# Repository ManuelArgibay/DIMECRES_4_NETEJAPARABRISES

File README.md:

# LIMPIA PARABRISAS

## Autores
- ManuelArgibay
- AlexY0916

## Versión - v1.01 Curso - Asignatura de Diseño de PCBs con KiCad - Curso 2024 - 2025

## Objectivo, Descripción breve del objectivo del proyecto.
Diseñar una placa PCB que desarrolle la función de limpiaparabrisas de un automóvil, mediante la detección de lluvia y accionamiento de motores, bombas de agua y un calefactor. Con el objetivo de mantener el parabrisas limpio y libre de objetos que puedan dificultar la visibilidad y evitar accidentes 

## Requisitos y especificaciones
- 2 motores con finales de carrera
- 2 bombas de líquido limpia parabrisas
- Sensor digital de lluvia
- Calefactor del vidrio

## Diagrama de bloques

## Tabla de componentes
| Descripción | Manufacturer Number | Package | Datasheet | Proveedor | Unidades |
| Microcontrolador | PIC18F258 | SOIC-28 | https://www.mouser.es/ProductDetail/Microchip-Technology/PIC18F258-I-SP?qs=uMUszenkLLIixFKqjRA69Q%3D%3D&srsltid=AfmBOopKXQlyaGkKwKApGVeNytftWyBSKV1Xqn-g4o59TgY9E8kJ9XiY | Mouser | 1 |
|Transceptor|MCP2551|SOIC-8|https://ww1.microchip.com/downloads/en/devicedoc/20001667g.pdf|Microchip|1|
|Amplificador operacional|LT1716|SOIC-5|https://www.mouser.es/datasheet/2/609/LT1716-1716222.pdf|Mouser|2|
|Regulador de tensión|LM117|TO-220|https://www.ti.com/lit/ds/symlink/lm1117.pdf?ts=1742942595976&ref_url=https%253A%252F%252Fbr.mouser.com%252F|Mouser|1|
|Puente H|DRV8871DDA|DDA|https://www.ti.com/lit/ds/symlink/drv8871-q1.pdf?ts=1742988697362&ref_url=https%253A%252F%252Fwww.ti.com%252Fproduct%252FDRV8871-Q1||2|

## Funcionalidades
- Control de motores de limpiaparabrisas, bomba de agua y calefactor
- Detección de lluvia mediante sensor
- Botonera de acción manual

## Historial de cambios | Fecha | Autor | Branch | Descripción |
|1|25/03/2025|ManuelArgibay|main|Creación del proyecto|
|2|25/03/2025|ManuelArgibay|main|Cambio titulo del proyecto|
|3|25/03/2025|ManuelArgibay|main|Modificación del esquemático y pptx|
|4|25/03/2025|ManuelArgibay|main|Agrego net classes, proyecto y presentación |
|5|25/03/2025|AlexY0916|main|Modifico net classes, fc, GNDPWR, separación botonera|
|6|26/03/2025|AlexY0916|main|Separacion del circuito|
|7|29/03/2025|ManuelArgibay|main|Agrego presentaciones y archivos|
|8|29/03/2025|ManuelArgibay|main|Modifico simulaciones del comparador y arreglo esquematico|
|9|30/03/2025|AlexY0916|main|Ordenar esquematico|
|10|30/03/2025|AlexY0916|main|Footprint|
|11|30/03/2025|AlexY0916|main|Arreglar errores con los esquematicos|
|12|30/03/2025|AlexY0916|main|Empezando a añadir el sensor|
|13|31/03/2025|AlexY0916|main|Sensor|
|14|31/03/2025|AlexY0916|main|ICSP|
|15|31/03/2025|ManuelArgibay|main|Arreglo net classes y agrego DB-9|
|16|31/03/2025|ManuelArgibay|main|Empiezo layout, cambio footprints y arreglo esquematico|
|17|01/04/2025|ManuelArgibay|main|Termino layout|
|18|01/04/2025|ManuelArgibay|main|Arreglo nodos no conectados|
|19|01/04/2025|AlexY0916|main|Cambio el cristal|
|20|01/04/2025|AlexY0916|main|Cambio de presentacion, minimas correcciones en el esquematico|
|21|01/04/2025|AlexY0916|main|Nombrar etiqueta PCB|
|22|01/04/2025|AlexY0916|main|Cambio en la presentacion|
|23|02/04/2025|ManuelArgibay|main|Arreglo errores y cambio conector|
|24|02/04/2025|ManuelArgibay|main|Arreglo errores del DRC. Falta arreglar errores del GNDPWR|
|25|02/04/2025|ManuelArgibay|main|Preentrega final|
|26|02/04/2025|ManuelArgibay|main|Agrego cambios|
|27|07/04/2025|ManuelArgibay|main|Arreglo layout y esquematico con las correcciones pasadas|
|28|07/04/2025|AlexY0916|main|Separacion de la botonera|
|29|07/04/2025|AlexY0916|main|Cambio de valor los condensadores del oscilador|
|30|07/04/2025|AlexY0916|main|Cambio diagrama de bloques|
|31|08/04/2025|AlexY0916|main|Reglas de diseño|
|32|08/04/2025|AlexY0916|main|Cambiar esquematico|
|33|08/04/2025|AlexY0916|main|Cambio de la PCB (cambio de conectores)|
|34|09/04/2025|AlexY0916|main|Layout|
|35|09/04/2025|AlexY0916|main|Cambio del sensor|
|36|23/04/2025|ManuelArgibay|main|Arreglo layout y esquematico (DRC correcto)|

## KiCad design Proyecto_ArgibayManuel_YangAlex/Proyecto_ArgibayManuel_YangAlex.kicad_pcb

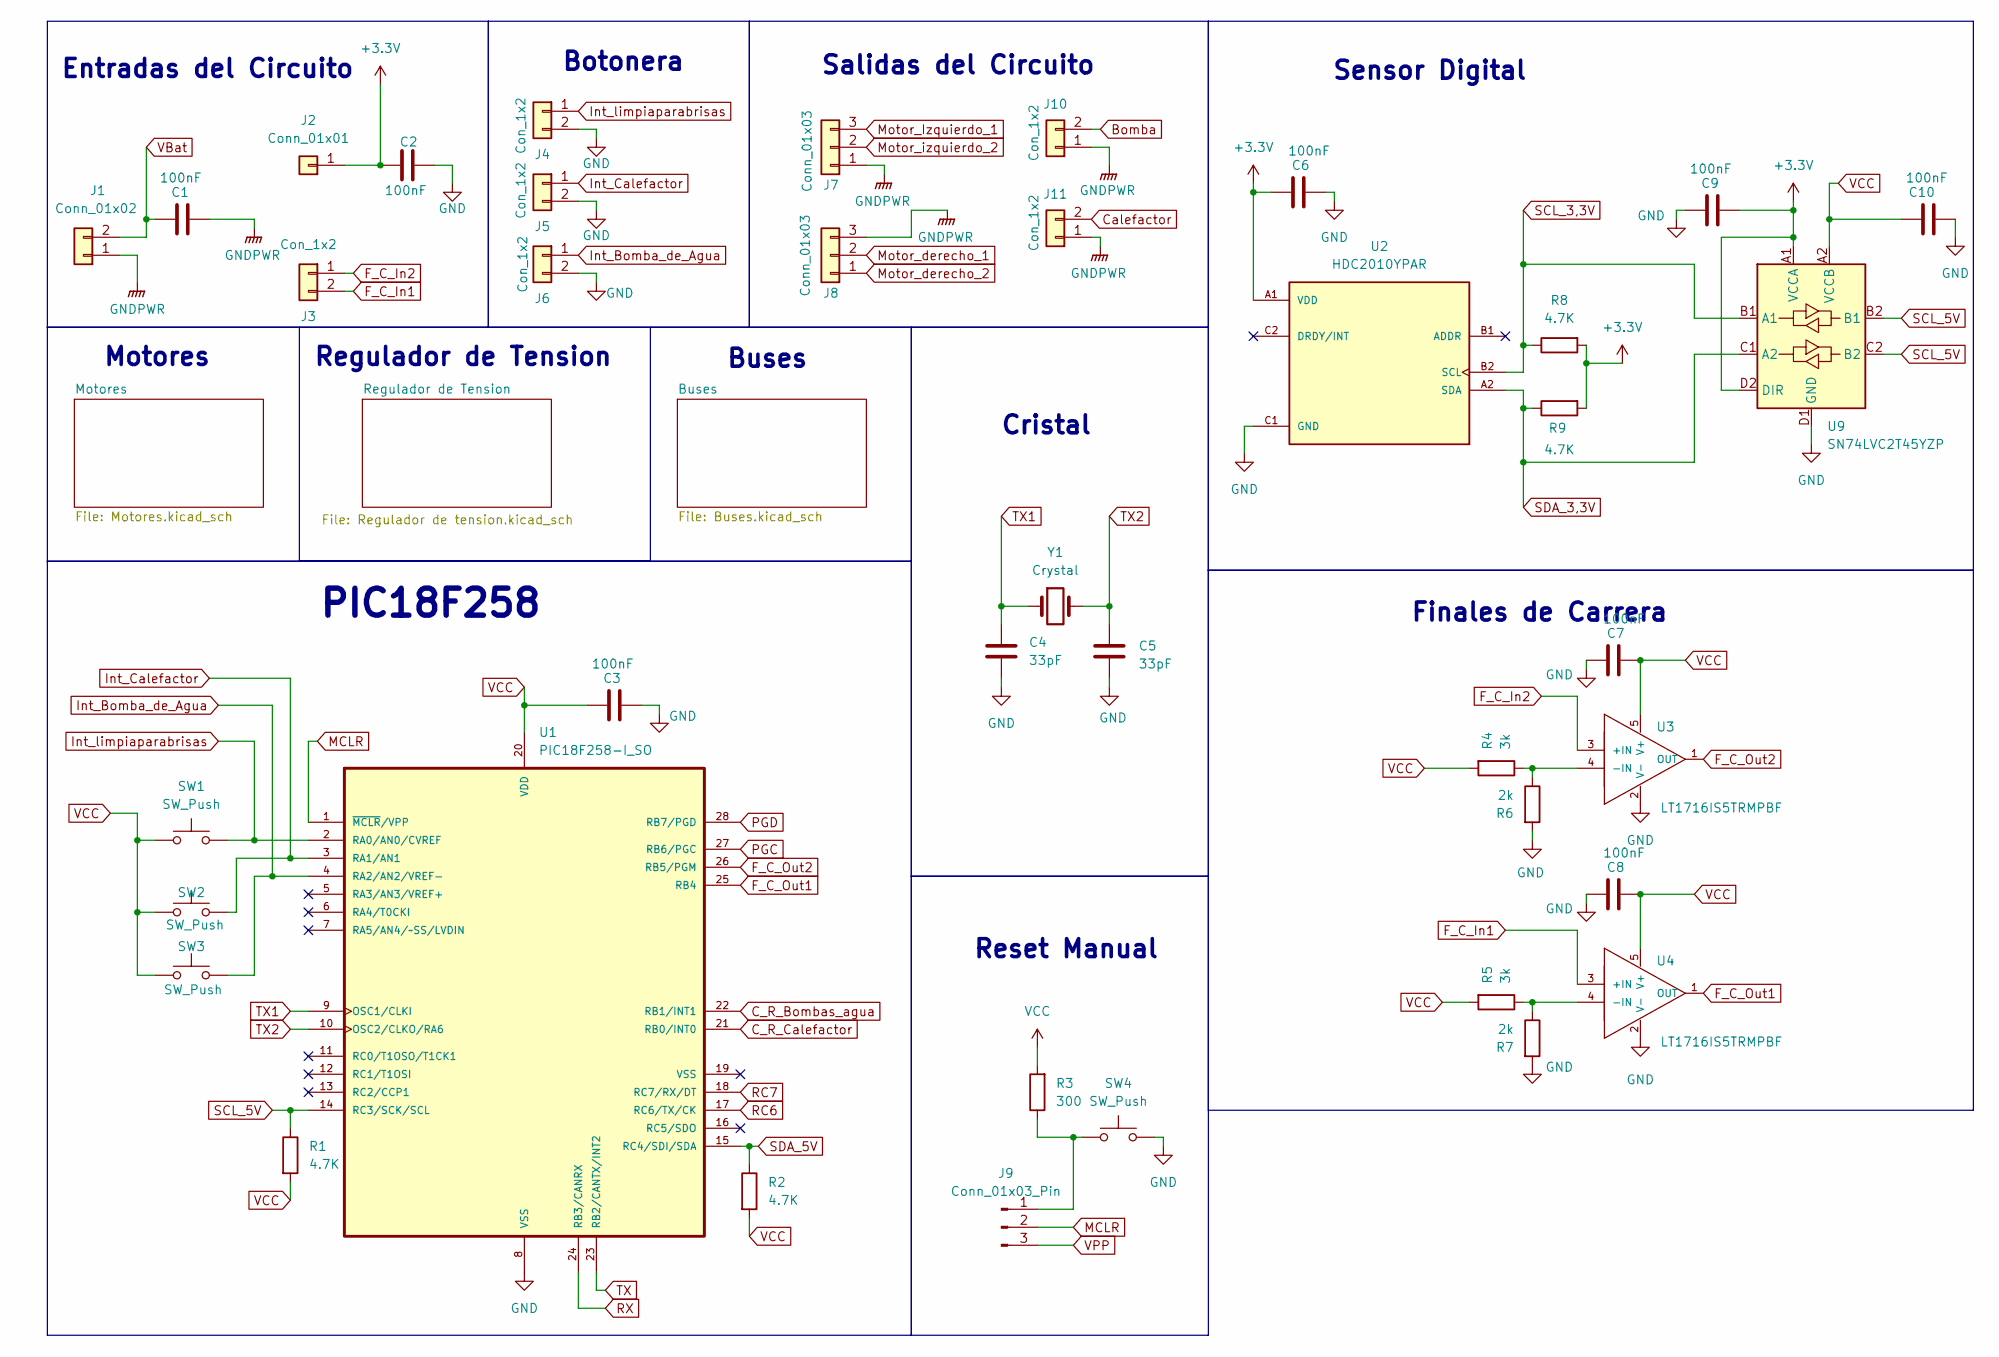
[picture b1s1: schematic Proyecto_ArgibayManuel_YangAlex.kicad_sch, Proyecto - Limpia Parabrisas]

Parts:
C1, C2, C3, C6, C7, C8, C9, C10: 100nF; C_0805_2012Metric
C4, C5: 33pF; C_0805_2012Metric
J1: Conn_01x02; PinHeader_1x02_P2.54mm_Vertical
J2: Conn_01x01; PinHeader_1x01_P2.54mm_Vertical
J3, J4, J5, J6: Con_1x2; PinHeader_1x02_P2.54mm_Vertical
J7, J8: Conn_01x03; TerminalBlock_Phoenix_MKDS-3-3-5.08_1x03_P5.08mm_Horizontal
J9: Conn_01x03_Pin; PinHeader_1x03_P2.54mm_Vertical
J10, J11: Con_1x2; TerminalBlock_Phoenix_MKDS-3-2-5.08_1x02_P5.08mm_Horizontal
R1, R2, R8, R9: 4.7K; R_0805_2012Metric
R3: 300; R_0805_2012Metric
R4, R5: 3k; R_0805_2012Metric
R6, R7: 2k; R_0805_2012Metric
SW1, SW2, SW3, SW4: SW_Push; SW_Push_1P1T_NO_CK_KMR2
U1: PIC18F258-I_SO; PIC18F258
U2: HDC2010YPAR; PARTREV C
U3, U4: LT1716IS5TRMPBF; LT1716; MANUFACTURER_PART_NUMBER lt1716is5#trmpbf; DIGIKEY_PART_NUMBER LT1716IS5#TRMPBFTRND
U9: SN74LVC2T45YZP; Texas_DSBGA-8_0.9x1.9mm_Layout2x4_P0.5mm
Y1: Crystal; Crystal_HC49-U_Vertical

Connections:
+3.3V: C2.1, C6.2, C9.2, J2.1, R8.2, R9.2, U2.A1 (VDD), U9.A1 (VCCA), U9.D2 (DIR)
Bomba: J10.2; also elsewhere on the board
C_R_Bombas_agua: U1.22 (RB1/INT1); also elsewhere on the board
C_R_Calefactor: U1.21 (RB0/INT0); also elsewhere on the board
Calefactor: J11.2; also elsewhere on the board
F_C_In1: J3.2, U4.3 (+IN)
F_C_In2: J3.1, U3.3 (+IN)
F_C_Out1: U1.25 (RB4), U4.1 (OUT)
F_C_Out2: U1.26 (RB5/PGM), U3.1 (OUT)
GND: C2.2, C3.2, C4.2, C5.2, C6.1, C7.2, C8.2, C9.1, C10.2, J4.2, J5.2, J6.2, R6.2, R7.2, SW4.2, U1.8 (VSS), U2.C1 (GND), U3.2 (V-), U4.2 (V-), U9.D1 (GND); also elsewhere on the board
GNDPWR: C1.2, J1.1, J7.1, J8.3, J10.1, J11.1; also elsewhere on the board
Int_Bomba_de_Agua: J6.1, SW3.2, U1.4 (RA2/AN2/VREF-)
Int_Calefactor: J5.1, SW2.2, U1.3 (RA1/AN1)
Int_limpiaparabrisas: J4.1, SW1.2, U1.2 (RA0/AN0/CVREF)
MCLR: J9.2, U1.1 (~MCLR/VPP)
Motor_Izquierdo_1: J7.3; also elsewhere on the board
Motor_derecho_1: J8.2; also elsewhere on the board
Motor_derecho_2: J8.1; also elsewhere on the board
Motor_izquierdo_2: J7.2; also elsewhere on the board
unnamed: J9.1, R3.1, SW4.1
unnamed: R4.1, R6.1, U3.4 (-IN)
unnamed: R5.1, R7.1, U4.4 (-IN)
PGC: U1.27 (RB6/PGC); also elsewhere on the board
PGD: U1.28 (RB7/PGD); also elsewhere on the board
RC6: U1.17 (RC6/TX/CK); also elsewhere on the board
RC7: U1.18 (RC7/RX/DT); also elsewhere on the board
RX: U1.24 (RB3/CANRX); also elsewhere on the board
SCL_5V: R1.1, U1.14 (RC3/SCK/SCL), U9.B2 (B1), U9.C2 (B2)
SDA_5V: R2.1, U1.15 (RC4/SDI/SDA)
TX: U1.23 (RB2/CANTX/INT2); also elsewhere on the board
TX1: C4.1, U1.9 (OSC1/CLKI), Y1.1
TX2: C5.1, U1.10 (OSC2/CLKO/RA6), Y1.2
VBat: C1.1, J1.2; also elsewhere on the board
VCC: C3.1, C7.1, C8.1, C10.1, R1.2, R2.2, R3.2, R4.2, R5.2, SW1.1, SW2.1, SW3.1, U1.20 (VDD), U3.5 (V+), U4.5 (V+), U9.A2 (VCCB); also elsewhere on the board
VPP: J9.3; also elsewhere on the board

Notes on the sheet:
Cristal
Entradas del Circuito
Sensor Digital
PIC18F258
Reset Manual
Salidas del Circuito
Regulador de Tension
Motores
Botonera
Buses
Finales de Carrera

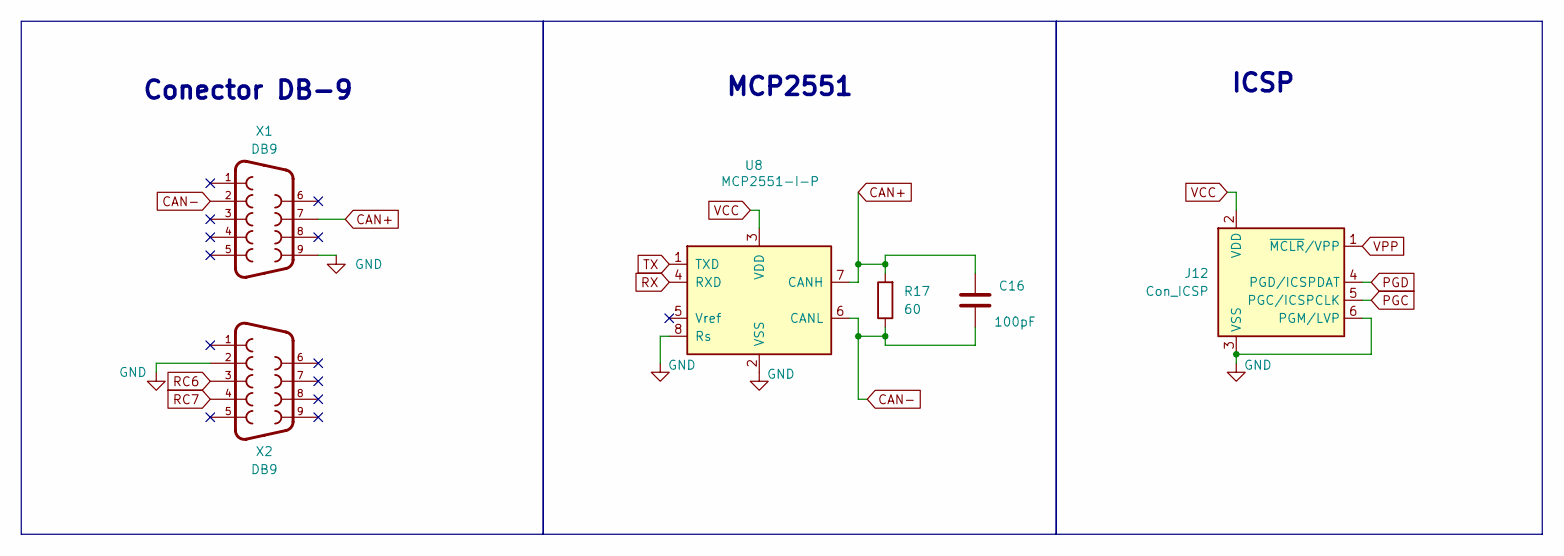
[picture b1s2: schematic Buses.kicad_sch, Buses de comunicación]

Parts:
C16: 100pF; C_0805_2012Metric
J12: Con_ICSP; PinHeader_1x06_P2.54mm_Vertical
R17: 60; R_0805_2012Metric
U8: MCP2551-I-P; DIP-8_W7.62mm
X1, X2: DB9

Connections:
CAN+: C16.2, R17.2, U8.7 (CANH), X1.7
CAN-: C16.1, R17.1, U8.6 (CANL), X1.2
GND: J12.3 (VSS), J12.6 (PGM/LVP), U8.2 (VSS), U8.8 (Rs), X1.9, X2.2; also elsewhere on the board
PGC: J12.5 (PGC/ICSPCLK); also elsewhere on the board
PGD: J12.4 (PGD/ICSPDAT); also elsewhere on the board
RC6: X2.3; also elsewhere on the board
RC7: X2.4; also elsewhere on the board
RX: U8.4 (RXD); also elsewhere on the board
TX: U8.1 (TXD); also elsewhere on the board
VCC: J12.2 (VDD), U8.3 (VDD); also elsewhere on the board
VPP: J12.1 (~MCLR/VPP); also elsewhere on the board

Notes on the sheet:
Conector DB-9
MCP2551
ICSP

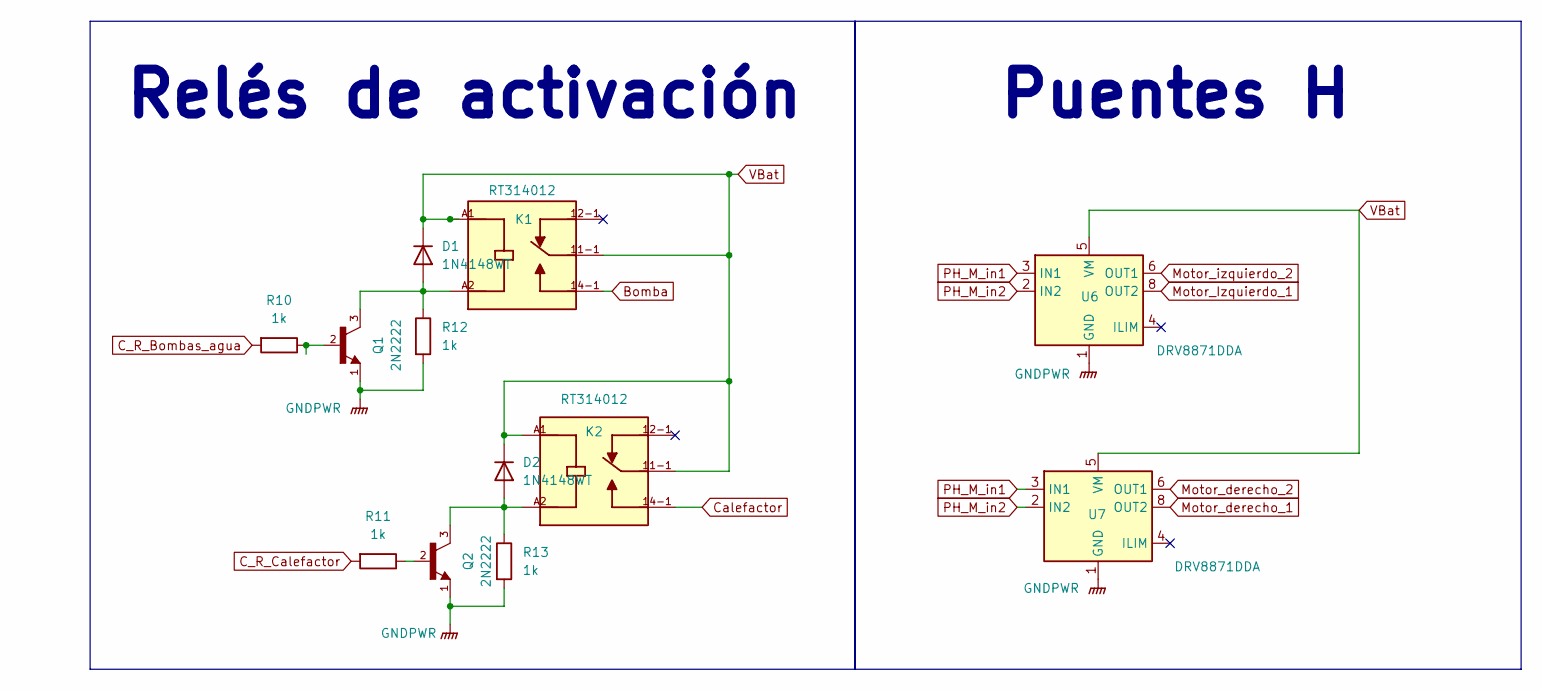
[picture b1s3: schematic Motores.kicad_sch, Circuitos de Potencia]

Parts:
D1, D2: 1N4148WT; D_SOD-523
K1, K2: RT314012; PARTREV 0120
Q1, Q2: 2N2222; PARTREV January 1989
R10, R11, R12, R13: 1k; R_0805_2012Metric
U6, U7: DRV8871DDA; Texas_HTSOP-8-1EP_3.9x4.9mm_P1.27mm_EP2.95x4.9mm_Mask2.4x3.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

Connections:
Bomba: K1.14-1; also elsewhere on the board
C_R_Bombas_agua: R10.2; also elsewhere on the board
C_R_Calefactor: R11.2; also elsewhere on the board
Calefactor: K2.14-1; also elsewhere on the board
GNDPWR: Q1.1, Q2.1, R12.2, R13.2, U6.1 (GND), U6.7 (GND), U6.9 (GND), U7.1 (GND), U7.7 (GND), U7.9 (GND); also elsewhere on the board
Motor_Izquierdo_1: U6.8 (OUT2); also elsewhere on the board
Motor_derecho_1: U7.8 (OUT2); also elsewhere on the board
Motor_derecho_2: U7.6 (OUT1); also elsewhere on the board
Motor_izquierdo_2: U6.6 (OUT1); also elsewhere on the board
unnamed: D1.2 (A), K1.A2, Q1.3, R12.1
unnamed: D2.2 (A), K2.A2, Q2.3, R13.1
unnamed: Q1.2, R10.1
unnamed: Q2.2, R11.1
PH_M_in1: U6.3 (IN1), U7.3 (IN1)
PH_M_in2: U6.2 (IN2), U7.2 (IN2)
VBat: D1.1 (K), D2.1 (K), K1.11-1, K1.A1, K2.11-1, K2.A1, U6.5 (VM), U7.5 (VM); also elsewhere on the board

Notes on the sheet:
Relés de activación
Puentes H

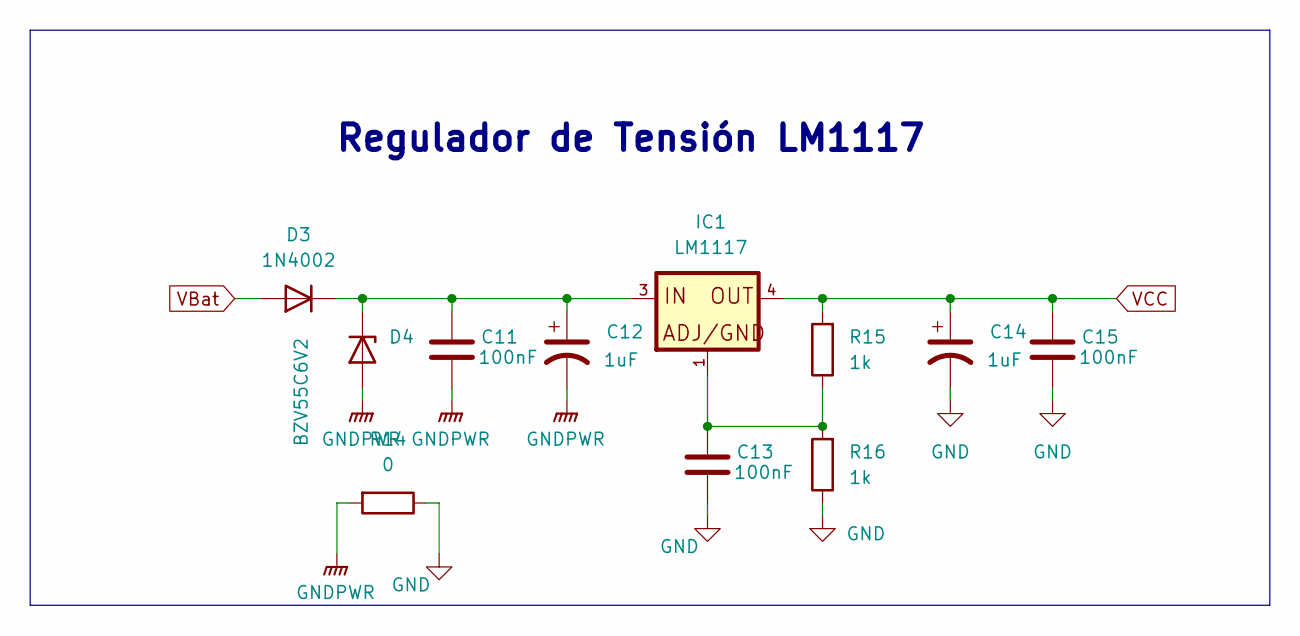
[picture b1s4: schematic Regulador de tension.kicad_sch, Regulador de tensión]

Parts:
C11, C13, C15: 100nF; C_0805_2012Metric
C12, C14: 1uF; C_0805_2012Metric
D3: 1N4002; D_DO-41_SOD81_P10.16mm_Horizontal
D4: BZV55C6V2; D_MiniMELF
IC1: LM1117
R14: 0; R_Axial_DIN0204_L3.6mm_D1.6mm_P5.08mm_Vertical
R15, R16: 1k; R_0805_2012Metric

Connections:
GND: C13.2, C14.2, C15.2, R14.1, R16.1; also elsewhere on the board
GNDPWR: C11.2, C12.2, D4.2 (A), R14.2; also elsewhere on the board
unnamed: C13.1, IC1.1, R15.1, R16.2
unnamed: C11.1, C12.1, D3.1 (K), D4.1 (K), IC1.3
VBat: D3.2 (A); also elsewhere on the board
VCC: C14.1, C15.1, IC1.4, R15.2; also elsewhere on the board

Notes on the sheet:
Regulador de Tensión LM1117

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
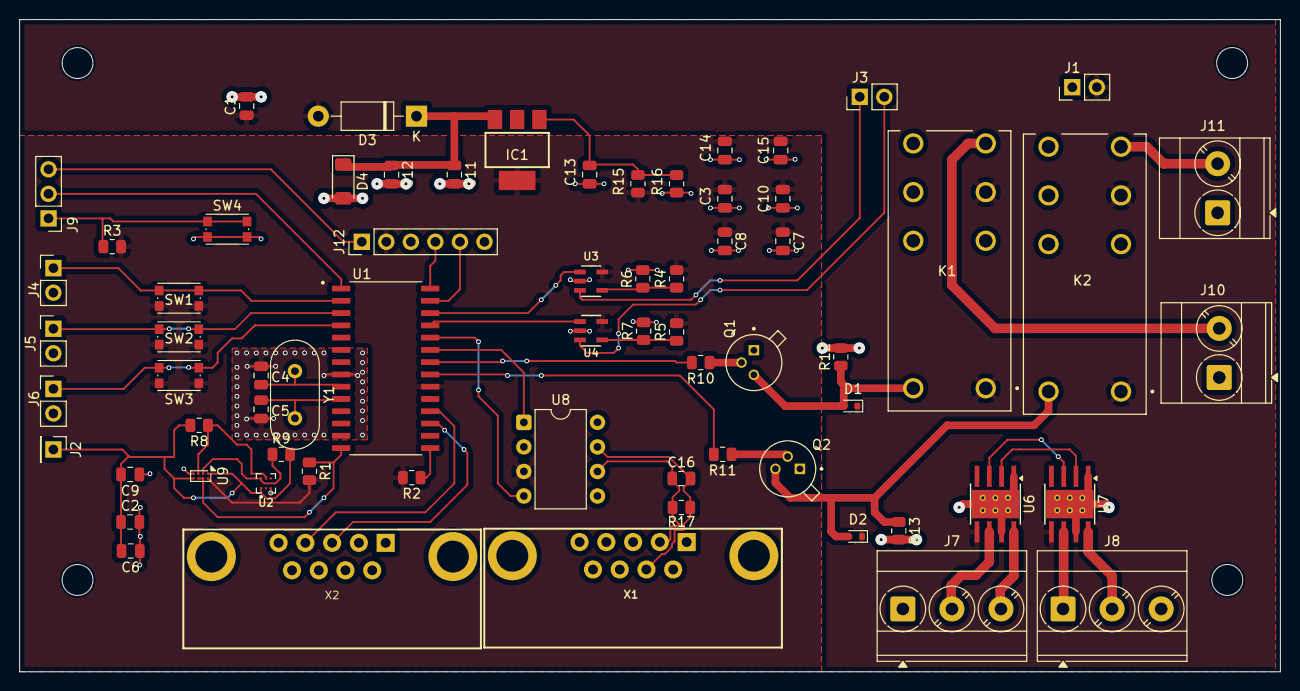
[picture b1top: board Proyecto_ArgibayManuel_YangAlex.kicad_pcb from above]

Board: 2 copper layers, 130.5 x 67.5 mm, 68 parts (0 on the bottom side), 47 nets.

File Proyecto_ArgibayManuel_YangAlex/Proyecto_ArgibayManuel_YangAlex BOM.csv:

"Reference","Qty","Value","DNP","Exclude from BOM","Exclude from Board","Footprint","Datasheet"
"C1,C2,C3,C6,C7,C8,C9,C10,C11,C13,C15","11","100nF","","","","Capacitor_SMD:C_0805_2012Metric","~"
"C4,C5","2","33pF","","","","Capacitor_SMD:C_0805_2012Metric","~"
"C12,C14","2","1uF","","","","Capacitor_SMD:C_0805_2012Metric","~"
"C16","1","100pF","","","","Capacitor_SMD:C_0805_2012Metric","~"
"D1,D2","2","1N4148WT","","","","Diode_SMD:D_SOD-523","https://www.diodes.com/assets/Datasheets/ds30396.pdf"
"D3","1","1N4002","","","","Diode_THT:D_DO-41_SOD81_P10.16mm_Horizontal","http://www.vishay.com/docs/88503/1n4001.pdf"
"D4","1","BZV55C6V2","","","","Diode_SMD:D_MiniMELF","https://assets.nexperia.com/documents/data-sheet/BZV55_SER.pdf"
"IC1","1","LM1117","","","","Footprints:LM1117",""
"J1","1","Conn_01x02","","","","Connector_PinHeader_2.54mm:PinHeader_1x02_P2.54mm_Vertical","~"
"J2","1","Conn_01x01","","","","Connector_PinHeader_2.54mm:PinHeader_1x01_P2.54mm_Vertical","~"
"J3,J4,J5,J6","4","Con_1x2","","","","Connector_PinHeader_2.54mm:PinHeader_1x02_P2.54mm_Vertical","~"
"J7,J8","2","Conn_01x03","","","","TerminalBlock_Phoenix:TerminalBlock_Phoenix_MKDS-3-3-5.08_1x03_P5.08mm_Horizontal","~"
"J9","1","Conn_01x03_Pin","","","","Connector_PinHeader_2.54mm:PinHeader_1x03_P2.54mm_Vertical","~"
"J10,J11","2","Con_1x2","","","","TerminalBlock_Phoenix:TerminalBlock_Phoenix_MKDS-3-2-5.08_1x02_P5.08mm_Horizontal","~"
"J12","1","Con_ICSP","","","","Connector_PinHeader_2.54mm:PinHeader_1x06_P2.54mm_Vertical","http://ww1.microchip.com/downloads/en/devicedoc/30277d.pdf"
"K1,K2","2","RT314012","","","","Footprints:RT314012",""
"Q1,Q2","2","2N2222","","","","Footprints:2N2222",""
"R1,R2,R8,R9","4","4.7K","","","","Resistor_SMD:R_0805_2012Metric","~"
"R3","1","300","","","","Resistor_SMD:R_0805_2012Metric","~"
"R4,R5","2","3k","","","","Resistor_SMD:R_0805_2012Metric","~"
"R6,R7","2","2k","","","","Resistor_SMD:R_0805_2012Metric","~"
"R10,R11,R12,R13,R15,R16","6","1k","","","","Resistor_SMD:R_0805_2012Metric","~"
"R14","1","0","","","","Resistor_THT:R_Axial_DIN0204_L3.6mm_D1.6mm_P5.08mm_Vertical","~"
"R17","1","60","","","","Resistor_SMD:R_0805_2012Metric","~"
"SW1,SW2,SW3,SW4","4","SW_Push","","","","Button_Switch_SMD:SW_Push_1P1T_NO_CK_KMR2","~"
"U1","1","PIC18F258-I_SO","","","","Footprints:PIC18F258",""
"U2","1","HDC2010YPAR","","","","Footprints:HDC2010YPAR",""
"U3,U4","2","LT1716IS5TRMPBF","","","","Footprints:LT1716",""
"U5","1","TXS0108EPW","","","","Package_SO:TSSOP-20_4.4x6.5mm_P0.65mm","www.ti.com/lit/ds/symlink/txs0108e.pdf"
"U6,U7","2","DRV8871DDA","","","","Package_SO:Texas_HTSOP-8-1EP_3.9x4.9mm_P1.27mm_EP2.95x4.9mm_Mask2.4x3.1mm_ThermalVias","http://www.ti.com/lit/ds/symlink/drv8871.pdf"
"U8","1","MCP2551-I-P","","","","Package_DIP:DIP-8_W7.62mm","http://ww1.microchip.com/downloads/en/devicedoc/21667d.pdf"
"X1,X2","2","DB9","","","","Footprints:DB9",""
"Y1","1","Crystal","","","","Crystal:Crystal_HC49-U_Vertical","~"

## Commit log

2025-03-25 Backlink to CADLAB.io has been added.
2025-03-25 Cambio título del proyecto
2025-03-26 Modificación de esquemático y presentación de pptx
2025-03-26 Agrego net classes, proyecto y cambio de presentación
2025-03-26 Modifique,netlist,Final de Carrera,GNDPWR,,seperar botonera
    Cambios
2025-03-26 Separacion del circuito
2025-03-29 Agrego presentaciones y archivos
2025-03-29 Modifico simulaciones del comparador y arreglo esquemático
2025-03-30 Ordenar esquematico
2025-03-30 footprint
2025-03-30 arreglar errores con los esquematicos
2025-03-30 empezando a añadir el sensor(aun no esta terminado)
2025-03-31 sensor
2025-03-31 icsp
2025-03-31 Arreglo net classes, agrego DB-9
2025-03-31 Modifico los footprints
2025-03-31 Empiezo layout, cambio footprints y arreglo esquematico
2025-03-31 Conexiones(no acabado)
2025-03-31 Cambio layout (faltan agregar vías y reorganizar con la capa BOTTOM)
2025-04-01 Termino layout (faltan acomodar etiquetas en la pcb))
2025-04-01 Arreglo nodos no conectados
2025-04-01 cambio del crystal
2025-04-01 Cambio de presentacion(esquematico,consumo,layout), minimas correciones en el esquematico
2025-04-01 nombrar etiqueta pcb
2025-04-01 Ligero cambio en la presentacion
2025-04-02 Arreglo errores y cambio conector
2025-04-02 Arreglo errores del DRC. falta arreglar errores del GNDPWR
2025-04-02 Preentrega final
2025-04-02 Agrego cambios
2025-04-07 Arreglo layout y esqumatico con las correcciones pasadas
2025-04-07 Separacion de Botonera
2025-04-07 cambio de valores de los Condensadores del oscilador
2025-04-07 cambio de diagrama de bloques
2025-04-08 Reglas de disenyo(requeriments)
2025-04-08 cambiar esquematico
2025-04-08 Cambio de la PCB(por el cambio de elos conectores)
2025-04-09 layout
2025-04-09 Cambio del sensor
2025-04-23 Arreglo layout y esquematico (DRC correcto)
2025-04-23 Empiezo presupuesto
2025-04-23 Cambio de Traductor bidireccional
2025-04-23 Presupuesto final y gerbers del layout
2025-04-23 traductor bidireccional(layout)
2025-04-23 Cambiamos traductor bidireccional
2025-04-23 Cambios en la presentacion
2025-04-30 final

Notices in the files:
parts and their libraries:
COPYRIGHT: Copyright C 2016 Accelerated Designs. All rights reserved
